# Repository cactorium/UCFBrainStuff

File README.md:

UCFBrainStuff
=============
UCF senior design project, schematic files and other things. Will be open sourced
at some point probably! All work is currently done in KiCAD but it may be converted
to a different EDA software

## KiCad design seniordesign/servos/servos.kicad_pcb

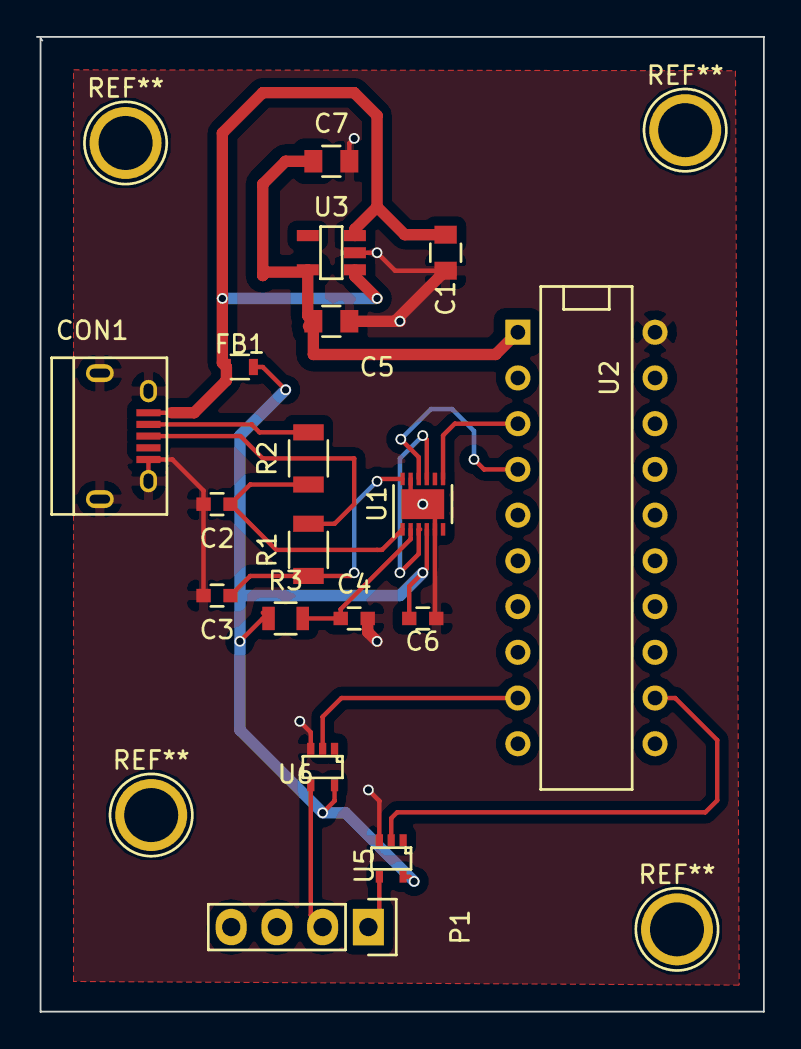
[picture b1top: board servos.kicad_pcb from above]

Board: 2 copper layers, 40.4 x 54.2 mm, 18 parts (0 on the bottom side), 16 nets.

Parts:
C1, C5: 22u; C_0805
C2, C3: 47p; C_0603
C4, C6: 100n; C_0603
C7: 0.1u; C_0805
CON1: USB-MICRO-B; USB_Micro-B
FB1: FERRITEBEAD; R_0603
P1: SERVO_PWMS; Pin_Header_Straight_1x04
R1, R2: 27; R_1206
R3: 10k; R_0805
U1: FT234XD; DFN-12-1EP_3x3mm_Pitch0.45mm
U2: MSP430G2153; DIP-20__300
U3: ADP151AUJZ-3.3-R7; TSOT-23
U5, U6: SN74LV1T04; sc70-5

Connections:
+5V: C6.1, FB1.1, R3.1, U1.4, U5.5, U6.5
GND: C1.2, C2.2, C3.2, C4.2, C5.2, C6.2, C7.2, CON1.5, CON1.6, CON1.7, CON1.8, CON1.9, U1.5, U1.11, U1.13, U2.20, U3.2, U5.3, U6.3
unnamed: C1.1, CON1.1, FB1.2, U3.1, U3.3
unnamed: C2.1, R2.1, U1.1
unnamed: C3.1, R1.1, U1.12
unnamed: C4.1, R3.2, U1.2
unnamed: C5.1, C7.1, U2.1, U3.5
unnamed: CON1.2, R2.2
unnamed: CON1.3, R1.2
unnamed: P1.1, U5.4
unnamed: P1.2, U6.4
unnamed: U1.3, U1.9
unnamed: U1.7, U2.3
unnamed: U1.10, U2.4
unnamed: U2.9, U6.2
unnamed: U2.12, U5.2

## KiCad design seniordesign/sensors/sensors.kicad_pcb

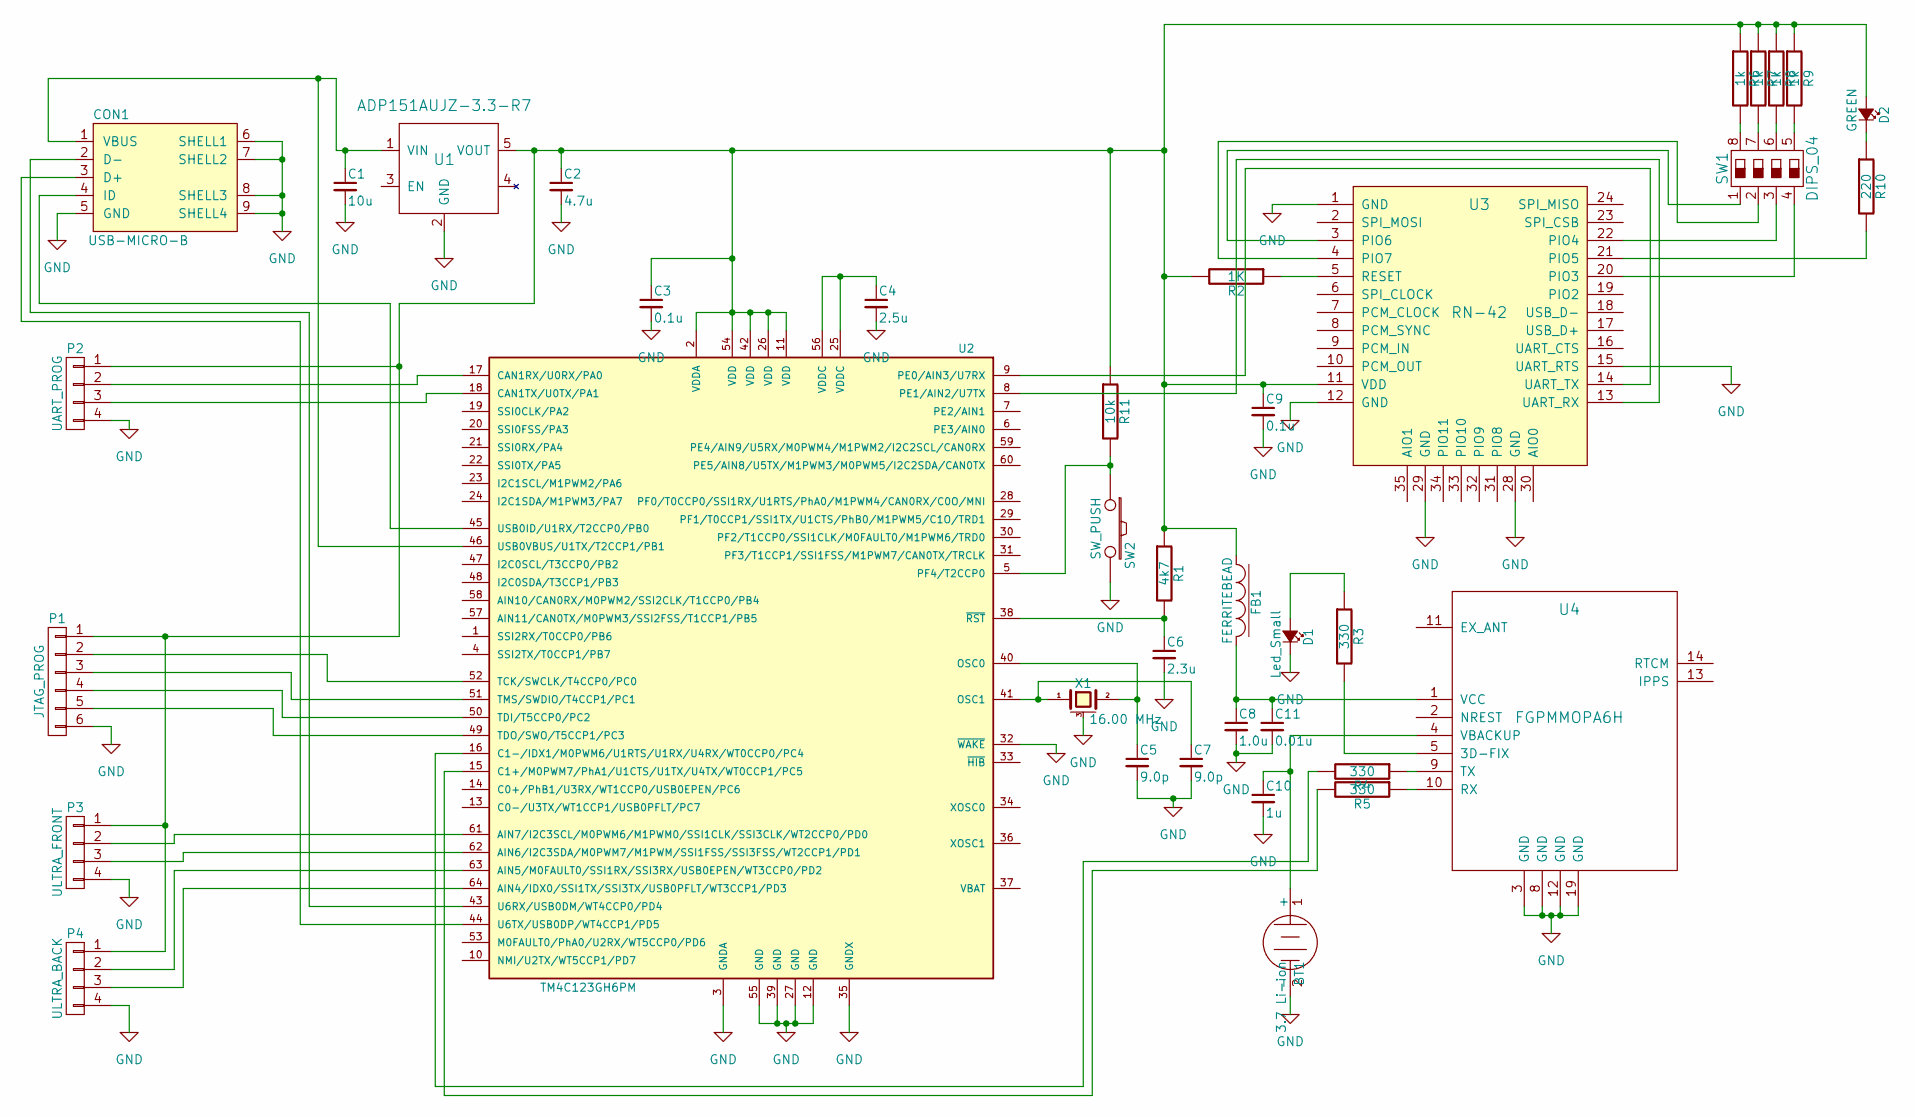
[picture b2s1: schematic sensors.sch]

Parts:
BT1: 3.7 Li-ion; BAT-HLD-001
C1: 10u; C_0805
C2: 4.7u; C_0603
C3, C9: 0.1u; C_0805
C4: 2.5u; C_0805
C5, C7: 9.0p; C_0603
C6: 2.3u; C_0603
C8: 1.0u; C_0805
C10: 1u; C_0603
C11: 0.01u; C_0603
CON1: USB-MICRO-B; USB_Micro-B
D1: Led_Small; C_0805
D2: GREEN; LED-1206
FB1: FERRITEBEAD; C_0805
P1: JTAG_PROG; Pin_Header_Straight_1x06
P2: UART_PROG; Pin_Header_Straight_1x04
P3: ULTRA_FRONT; Pin_Header_Straight_1x04
P4: ULTRA_BACK; Pin_Header_Straight_1x04
R1: 4k7; R_0805
R2: 1K; R_0603
R3, R4, R5: 330; R_0805
R6, R7, R8, R9: 1k; R_0603
R10: 220; R_0805
R11: 10k; R_0805
SW1: DIPS_04; SDA04H1BD
SW2: SW_PUSH; 1571634-1
U1: ADP151AUJZ-3.3-R7; SOT-23-5
U2: TM4C123GH6PM; LQFP-64_10x10mm_Pitch0.5mm
U3: RN-42; RovingNetworks_RN-42
U4: FGPMMOPA6H; GlobalTop-FGPMMOPA6H
X1: 16.00 MHz; crystal_FA238-TSX3225

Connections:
GND: BT1.2 (-), C1.2, C2.2, C3.2, C4.2, C5.2, C6.2, C7.2, C8.2, C9.2, C10.2, C11.2, CON1.5 (GND), CON1.6 (SHELL1), CON1.7 (SHELL2), CON1.8 (SHELL3), CON1.9 (SHELL4), D1.2 (C), P1.6, P2.4, P3.4, P4.4, SW2.2, U1.2 (GND), U2.3 (GNDA), U2.12 (GND), U2.27 (GND), U2.32 (~WAKE~), U2.35 (GNDX), U2.39 (GND), U2.55 (GND), U3.1 (GND), U3.12 (GND), U3.15 (UART_RTS), U3.28 (GND), U3.29 (GND), U4.3 (GND), U4.8 (GND), U4.12 (GND), U4.19 (GND), X1.3 (case)
unnamed: BT1.1 (+), C10.1, U4.4 (VBACKUP)
unnamed: C2.1, C3.1, C9.1, D2.1 (A), FB1.1, P1.1, P2.1, P3.1, P4.1, R1.1, R2.2, R6.1, R7.1, R8.1, R9.1, R11.1, U1.5 (VOUT), U2.2 (VDDA), U2.11 (VDD), U2.26 (VDD), U2.42 (VDD), U2.54 (VDD), U3.11 (VDD)
unnamed: C4.1, U2.25 (VDDC), U2.56 (VDDC)
unnamed: C5.1, U2.40 (OSC0), X1.2
unnamed: C6.1, R1.2, U2.38 (~RST~)
unnamed: C7.1, U2.41 (OSC1), X1.1
unnamed: C8.1, C11.1, FB1.2, U4.1 (VCC)
unnamed: CON1.2 (D-), U2.43 (U6RX/USB0DM/WT4CCP0/PD4)
unnamed: CON1.3 (D+), U2.44 (U6TX/USB0DP/WT4CCP1/PD5)
unnamed: CON1.4 (ID), U2.45 (USB0ID/U1RX/T2CCP0/PB0)
unnamed: D1.1 (A), R3.1
unnamed: D2.2 (C), R10.1
unnamed: P1.2, U2.52 (TCK/SWCLK/T4CCP0/PC0)
unnamed: P1.3, U2.51 (TMS/SWDIO/T4CCP1/PC1)
unnamed: P1.4, U2.50 (TDI/T5CCP0/PC2)
unnamed: P1.5, U2.49 (TDO/SWO/T5CCP1/PC3)
unnamed: P2.2, U2.17 (CAN1RX/U0RX/PA0)
unnamed: P2.3, U2.18 (CAN1TX/U0TX/PA1)
unnamed: P3.2, U2.61 (AIN7/I2C3SCL/M0PWM6/M1PWM0/SSI1CLK/SSI3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)
unnamed: P3.3, U2.62 (AIN6/I2C3SDA/M0PWM7/M1PWM/SSI1FSS/SSI3F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)
unnamed: P4.2, U2.63 (AIN5/M0FAULT0/SSI1RX/SSI3RX/USB0EPEN/WT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)
unnamed: P4.3, U2.64 (AIN4/IDX0/SSI1TX/SSI3TX/USB0PFLT/WT3CCP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)
unnamed: R2.1, U3.5 (RESET)
unnamed: R3.2, U4.5 (3D-FIX)
unnamed: R4.1, U4.9 (TX)
unnamed: R4.2, U2.16 (C1-/IDX1/M0PWM6/U1RTS/U1RX/U4RX/WT0CCP0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)
unnamed: R5.1, U4.10 (RX)
unnamed: R5.2, U2.15 (C1+/M0PWM7/PhA1/U1CTS/U1TX/U4TX/WT0CCP1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)
unnamed: R6.2, SW1.8
unnamed: R7.2, SW1.7
unnamed: R8.2, SW1.6
unnamed: R9.2, SW1.5
unnamed: R10.2, U3.21 (PIO5)
unnamed: R11.2, SW2.1, U2.5 (PF4/T2CCP0)
unnamed: SW1.1, U3.3 (PIO6)
unnamed: SW1.2, U3.4 (PIO7)
unnamed: SW1.3, U3.22 (PIO4)
unnamed: SW1.4, U3.20 (PIO3)
unnamed: U2.8 (PE1/AIN2/U7TX), U3.13 (UART_RX)
unnamed: U2.9 (PE0/AIN3/U7RX), U3.14 (UART_TX)

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
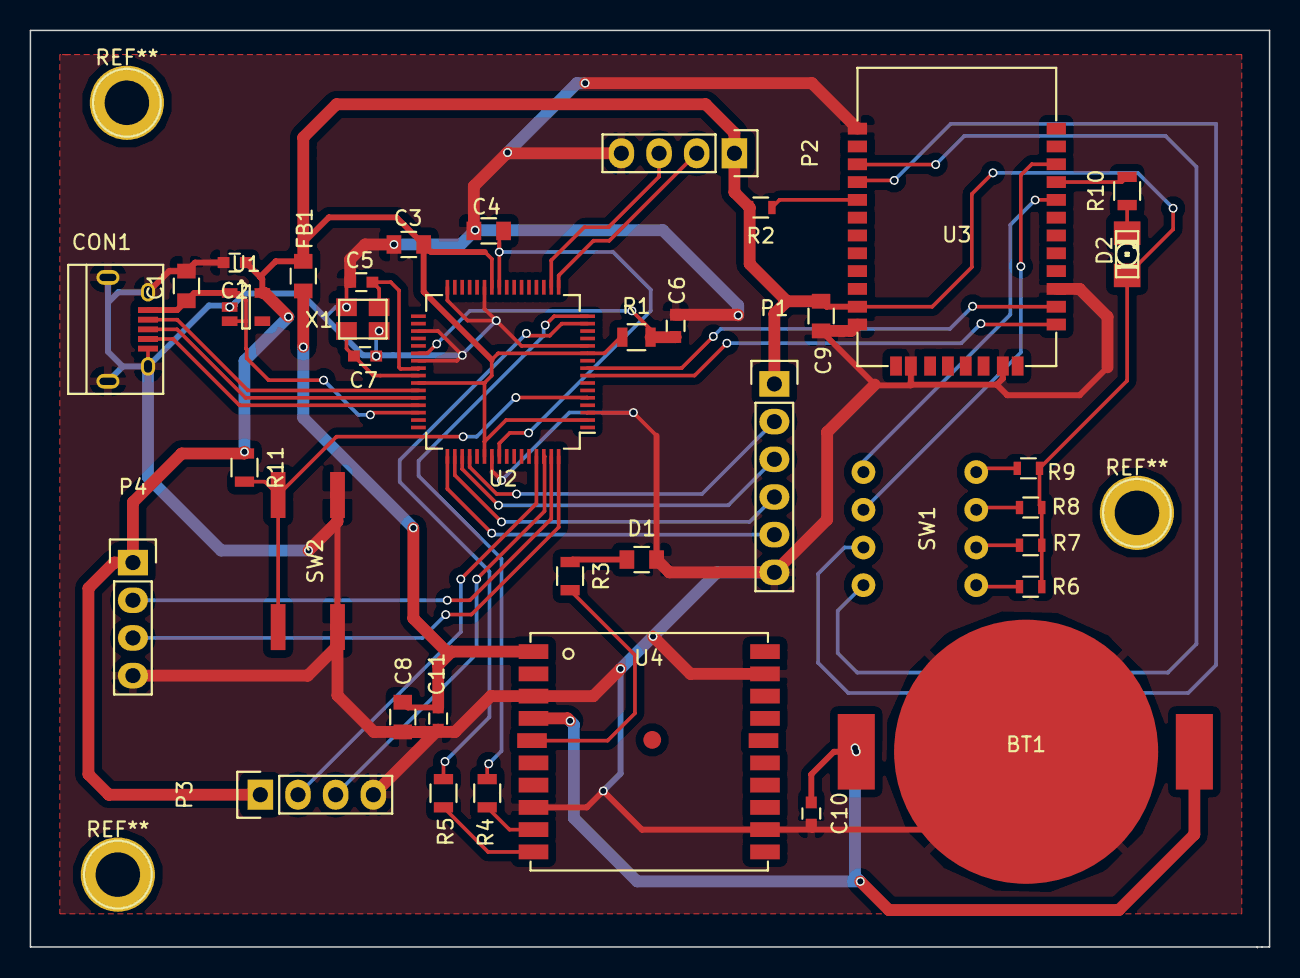
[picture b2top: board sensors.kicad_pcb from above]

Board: 2 copper layers, 83.5 x 61.8 mm, 38 parts (0 on the bottom side), 42 nets.

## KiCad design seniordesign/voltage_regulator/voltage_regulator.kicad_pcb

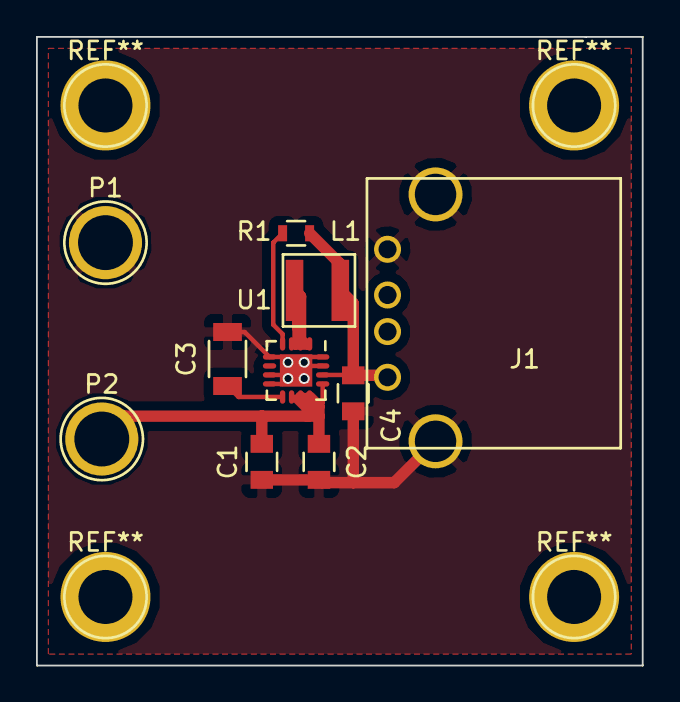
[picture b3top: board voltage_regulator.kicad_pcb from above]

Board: 2 copper layers, 33.7 x 34.9 mm, 10 parts (0 on the bottom side), 6 nets.

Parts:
C1: 10u; C_0805
C2: 0.1u; C_0805
C3: 3.3n; C_1206
C4: 22u; C_0805
J1: USB; USB_A
L1: 22u; Coilcraft_XFL4020
P1: GND; 1pin
P2: BATT+; 1pin
R1: 100k; R_0603
U1: TPS62133; QFN-16-1EP_3x3mm_Pitch0.5mm

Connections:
GND: C1.2, C2.2, C3.2, C4.2, J1.4, J1.5, J1.6, P1.1, U1.5, U1.7, U1.8, U1.15, U1.16, U1.17
unnamed: C1.1, C2.1, P2.1, U1.10, U1.11, U1.12, U1.13
unnamed: C3.1, U1.9
unnamed: C4.1, J1.1, L1.2, R1.1, U1.14
unnamed: L1.1, U1.1, U1.2, U1.3
unnamed: R1.2, U1.4

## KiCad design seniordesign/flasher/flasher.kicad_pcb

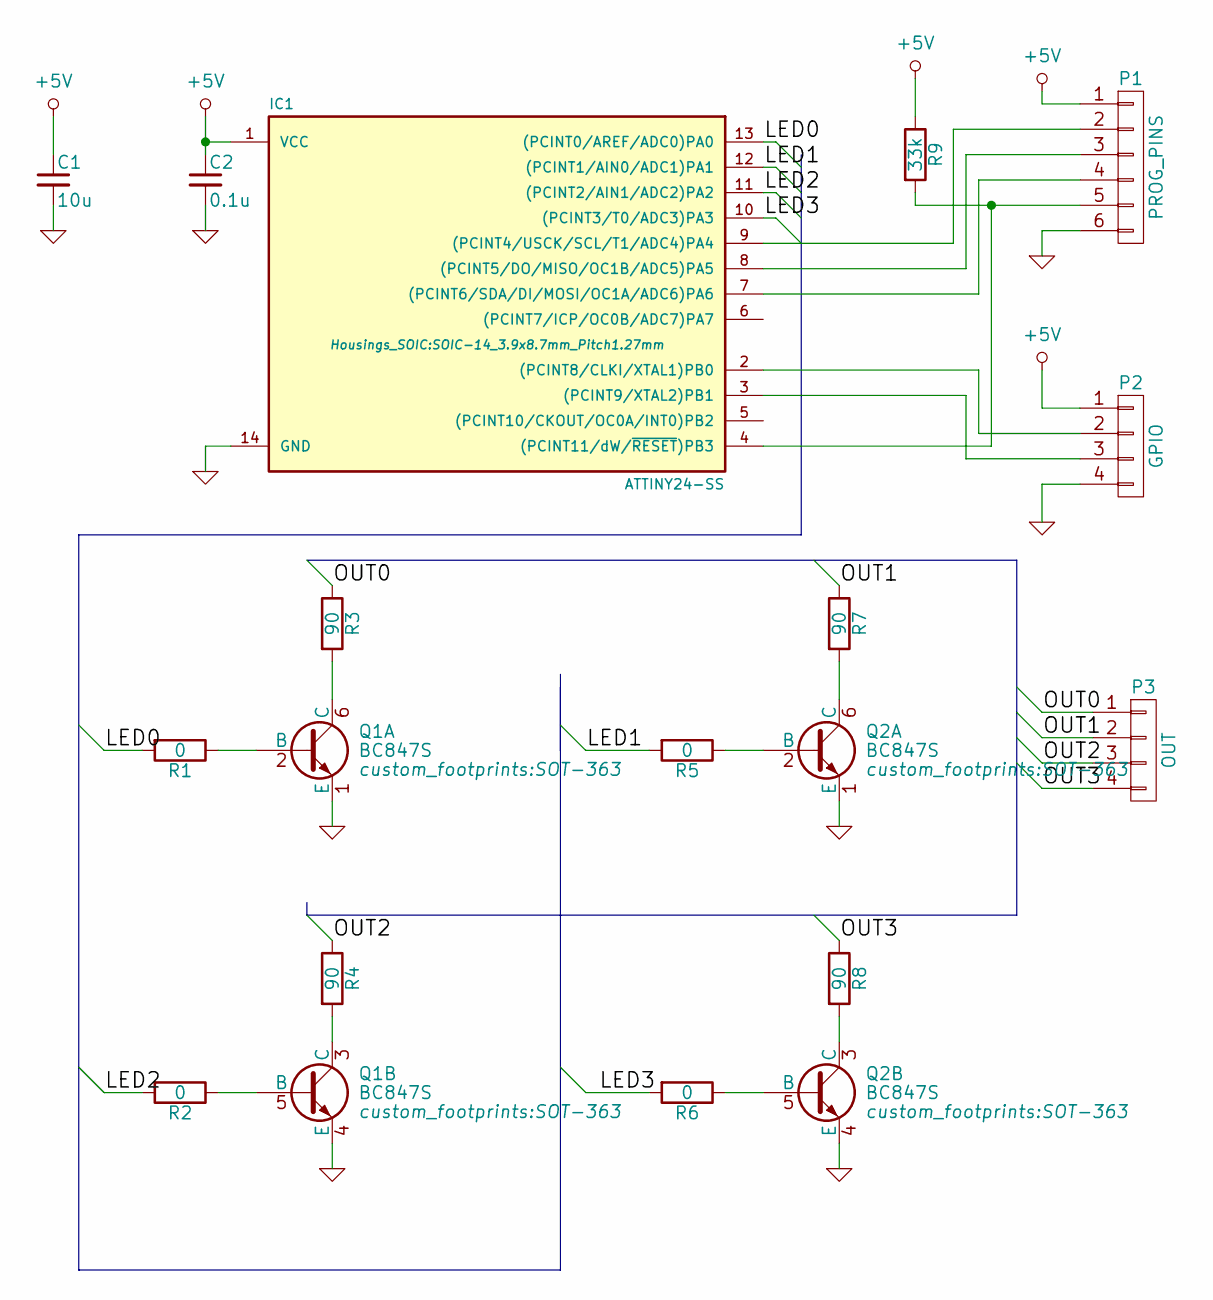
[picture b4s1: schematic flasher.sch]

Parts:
C1: 10u; C_0805
C2: 0.1u; C_0805
IC1: ATTINY24-SS; SOIC-14_3.9x8.7mm_Pitch1.27mm
P1: PROG_PINS; Pin_Header_Straight_1x06
P2: GPIO; SolderWirePad_4xInline_1-2mmDrill
P3: OUT; SolderWirePad_4xInline_2mmDrill
Q1, Q2: BC847S; SOT-363
R1, R2, R5, R6: 0; R_0805
R3, R4, R7, R8: 90; R_0805
R9: 33k; R_0805

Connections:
+5V: C1.1, C2.1, IC1.1 (VCC), P1.1, P2.1, R9.1
/LED0: IC1.13 ((PCINT0/AREF/ADC0)PA0), R1.2
/LED1: IC1.12 ((PCINT1/AIN0/ADC1)PA1), R5.2
/LED2: IC1.11 ((PCINT2/AIN1/ADC2)PA2), R2.2
/LED3: IC1.10 ((PCINT3/T0/ADC3)PA3), R6.2
/OUT0: P3.1, R3.1
/OUT1: P3.2, R7.1
/OUT2: P3.3, R4.1
/OUT3: P3.4, R8.1
GND: C1.2, C2.2, IC1.14 (GND), P1.6, P2.4, Q1.1 (E), Q1.4 (E), Q2.1 (E), Q2.4 (E)
unnamed: IC1.2 ((PCINT8/CLKI/XTAL1)PB0), P2.2
unnamed: IC1.3 ((PCINT9/XTAL2)PB1), P2.3
unnamed: IC1.4 ((PCINT11/dW/~RESET~)PB3), P1.5, R9.2
unnamed: IC1.7 ((PCINT6/SDA/DI/MOSI/OC1A/ADC6)PA6), P1.4
unnamed: IC1.8 ((PCINT5/DO/MISO/OC1B/ADC5)PA5), P1.3
unnamed: IC1.9 ((PCINT4/USCK/SCL/T1/ADC4)PA4), P1.2
unnamed: Q1.2 (B), R1.1
unnamed: Q1.3 (C), R4.2
unnamed: Q1.5 (B), R2.1
unnamed: Q1.6 (C), R3.2
unnamed: Q2.2 (B), R5.1
unnamed: Q2.3 (C), R8.2
unnamed: Q2.5 (B), R6.1
unnamed: Q2.6 (C), R7.2

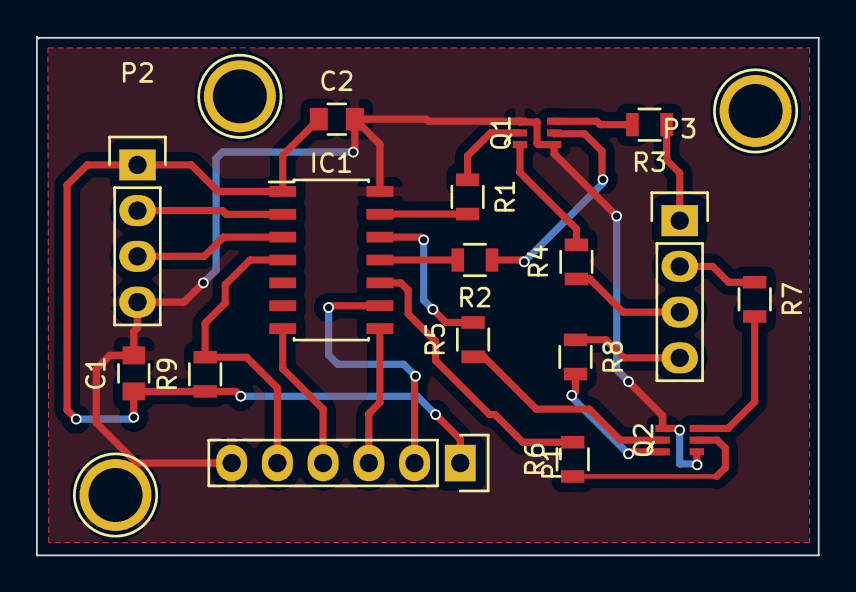
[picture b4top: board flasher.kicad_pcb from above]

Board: 2 copper layers, 43.4 x 28.8 mm, 17 parts (0 on the bottom side), 24 nets.

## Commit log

2014-12-14 Added all the files we had before
2014-12-15 Improved performance of SEIZURES.htm
2015-02-28 Last commit before restructuring
2015-02-28 Added emokit as submodule
2015-02-28 Ignoring Cmake files
2015-02-28 Use more appropriate .gitignore entries
2015-02-28 Clean up .gitignore
2015-02-28 Move old Python files to subdir
2015-02-28 Almost working cmakes config
2015-02-28 Fully CMake build!
2015-03-01 Working build with some API functions
2015-03-01 Added EEG channel mask declarations
2015-03-01 v1. of API
2015-03-01 All stream API functions declared and generic functions implemented
2015-03-01 Most generic library functions implemented
2015-03-12 Test on new computer
2015-03-18 Initial Commit
    Doesn't work yet...
2015-03-23 FOUR SEIZURES FOR THE PRICE OF ONEgit status!
2015-03-23 MORE CONFIGURABLE SEIZURES
2015-07-31 Add git repo
2015-07-31 Really add schematics
2015-07-31 Clean directory tree; this repo is now focused mainly on the hardware
2015-08-22 Fix library break, I think?
2015-08-24 Fix footprint library tables more
2015-08-24 Fix everything in sensors except the DIP switch, battery holder, and LED
2015-08-24 Fix flasher; now generates footprints successfully!
2015-08-24 Add more stuff to servos
2015-08-24 Working servos schematic; can generate footprints!
2015-08-24 voltage_regulator is fully footprinted!
2015-08-24 Fix sensors; footprints are now correct (probably)!
2015-08-24 Fix README and LICENSE
2015-08-24 Design servo PCB and generate Gerber files for it
2015-08-25 Add proper bypass cap pair for GPS
2015-08-25 Thicken some of the power traces in the servo board
2015-08-25 Add pushbutton to program TM4C123[...]
2015-08-25 Generate PCB/Gerber files for voltage regulator circuit
2015-08-27 Start work on design generator
2015-08-27 Based cutout generator finished. That's like, 10% of the way there?
2015-08-27 Generated front bearing
2015-08-27 Base successfully generated
2015-08-27 Halfway done on azimuthal arm
2015-08-27 Generate azimuthal struts
2015-08-27 Generate mounts for azimuthal arm
2015-08-27 Change placement slightly
2015-08-28 Generate elevator arms
2015-08-28 Generate struts for elevator arm
2015-08-28 Add slots to azimuthal arms
2015-08-28 Finished gimbal design generator!
2015-08-28 Fix base plate and some other stuff
2015-08-28 Fix servo mounts
2015-08-28 Change precision, extend the height of elevator end struts
2015-08-28 Finish second version of gimbal
2015-09-02 Add sensor PCB Gerber files
2015-09-03 Cameron: make flasher PCB
2015-09-04 Switch to new servo dimensions
2015-09-05 Add test assembly code
2015-09-07 Failed hardware UART/hardware PWM
2015-09-07 UART and PWM working together!
2015-09-07 Working gimbal test
2015-09-08 Fix servo stuff, regenerate Gerber files for everything
2015-09-09 Update schematic SVGs
2015-09-09 Removed redundant SVGs
2015-09-11 Regenerate all Gerber files, add edge cuts and solder mask
2015-09-11 Super master board created!
2015-09-11 Save Gerber files ,revision 9
2015-09-12 Add revised version of PCBs
2015-09-12 Ignore ZIP files here
2015-09-12 Generate Gerber files
2015-09-12 Adding some emokit stuff for A A RON
2015-09-16 Final master Gerber files before shipping
2015-09-16 Add start of processing file
2015-09-16 Remove ropeproject files
2015-09-16 Sample code running
2015-09-16 Framework set up
2015-09-16 added some stuff to eeg.py. It's not currently working
2015-10-02 Update svgs
